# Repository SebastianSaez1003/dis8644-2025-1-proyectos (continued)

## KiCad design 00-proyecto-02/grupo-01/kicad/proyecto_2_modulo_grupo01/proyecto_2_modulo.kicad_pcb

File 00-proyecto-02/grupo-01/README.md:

# proyecto-02

## Acerca del proyecto

- Grupo: 01
- Integrantes:
  - Emilia Contreras / [hazzaily](https://github.com/hazzaily)
  - Katalina Riquelme / [katalinariquelme](https://github.com/katalinariquelme)
  - Thyare Santander / [thyare08](https://github.com/thyare08)
- Chips usados:
  - Chip 555
  - Chip 4017
  - Chip LM324

## Presentación textual

Luz de noche en secuencia gradual con forma de nube.

El proyecto consiste en un detector de sombra invertido que enciende una lámpara que posee una secuencia gradual.

## Dibujos de diagramas del circuito (1 punto)

Este es el diagrama a mano.

En este  dibujo mostramos en orden cómo se efectúa la secuencia de luces o no, según sea que esté en una habitación con luz u oscuridad.

## Prototipado de circuitos en protoboard (1 punto)

A continuación se presentan imágenes de las protoboards usadas.

En la protoboard larga está configurado el detector de sombras, en el cual se utiliza un LDR para encender si está oscuro y apagarse si hay luz. Luego viene el chip 555 con un potenciómetro que regula la intesidad de la luz, continuando con un LM324 que crea la secuencia de las luces. Finalizamos el circuito de salida usando transistores que hicieron que al encender y apagarlos LED se prendieran y apagaran de manera gradual.

## Bill of Materials (1 punto)

| Reference                                       | Value   | Qty |
|-------------------------------------------------|---------|-----|
| C1,C3,C4                                        | 10uF    | 3   |
| C2                                              | 103n    | 1   |
| C7,C8,C9,C10,C11,C12                            | 220uF   | 6   |
| D5,D6,D7,D8,D9,D10,D11,D12,D13,D14,D15,D16      | LED 5mm | 12  |
| J1                                              | ph-2    | 1   |
| J5,J6,J7                                        | ph-3    | 2   |
| J21,J23                                         | mod1    | 2   |
| J22,J24                                         | mod2    | 2   |
| J25,J26                                         | mod3    | 2   |
| Q2,Q3,Q4                                        | 2n2222  | 3   |
| R1,R3,R4,R7,R8                                  | 10k     | 5   |
| R2                                              | LDR     | 1   |
| R5                                              | 100K    | 1   |
| R15,R17,R22,R25,R27,R31                         | 47K     | 6   |
| R16,R18,R19,R20,R21,R23,R24,R26,R28,R29,R30,R32 | 1K      | 12  |
| RV1,RV2                                         | 500K    | 2   |
| U1                                              | LM324   | 1   |
| U2                                              | 555     | 1   |
| U3                                              | 4017    | 1   |

## Ayudas y comunicación con colegas (1 punto)

[FranUDP](https://github.com/FranUDP) nos ayudó a revisar nuestro esquemático, a buscar y asignar huellas, y además de ayudarnos a resolver dudas sobre la PCB.

[Bernardita-lobo](https://github.com/Bernardita-lobo) y [jotamorales-romulus](https://github.com/jotamorales-romulus) nos ayudaron con el registro fotográfico de nuestra protoboard.

[duckusu](https://github.com/duckusu) nos ayudó a busacr lugares en donde podríamos comprar materiales faltantes, y por mayor.

Ayudamos a [antocristi](https://github.com/antocristi) y a [paulinavargasf](https://github.com/paulinavargasf) del grupo 05 a saber cómo subir fotos a los archivos de github.

## Esquematico en Kicad (1 punto)

El esquemático comienza con un chip LM324, el cual funciona como detector de luz, esto porque es la configuración inicial de un detector de sombra, pero con R1 y R2 intercambiados, logrando así que el circuito se encienda cuando no haya luz estimulando el LDR. El chip siguiente es un 555 configurado en modo astable, lo que nos permite controlar la velocidad con la que cambia la "tira de LED" a la siguiente. Seguido de esto tenemos un chip 4017 que funciona como secuenciador, siendo esta secuencia de "tiras de LED" la que controla el chip anterior. Por último, gracias al uso de transistores es que logramos una iluminación que va de menor a mayor, y cuando se apaga de mayor a menor, generando una onda que cambia suavemente y no de manera abrupta.

## PCB en Kicad (1 punto)

## Recursos adicionales

## Bibliografía

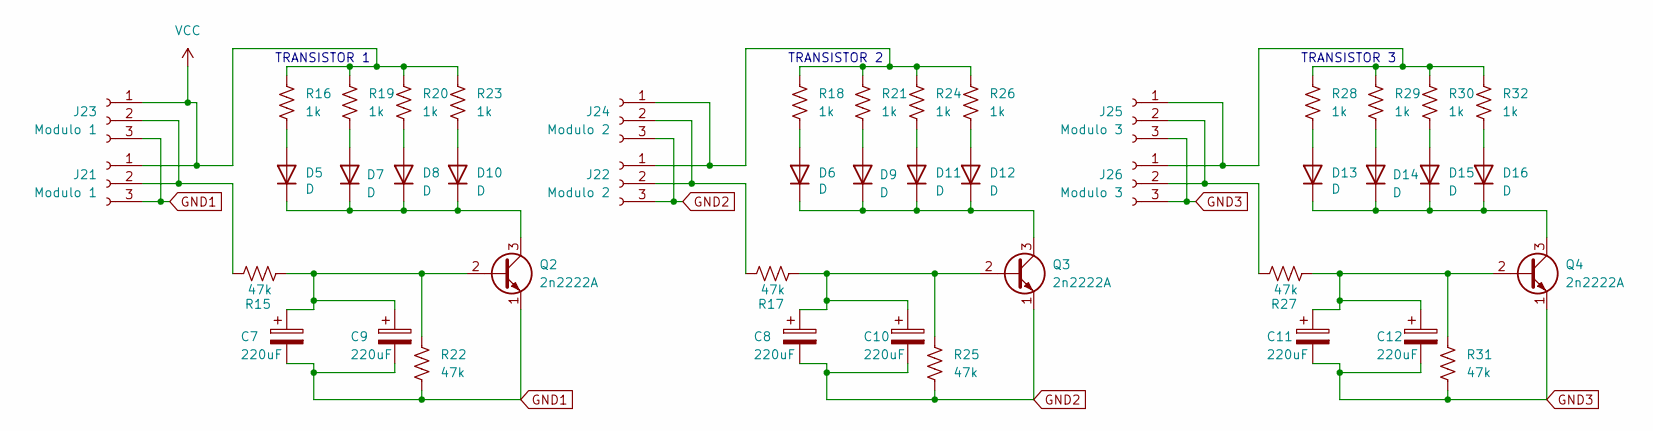
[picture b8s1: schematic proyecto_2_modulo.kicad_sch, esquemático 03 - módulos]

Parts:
C7, C8, C9, C10, C11, C12: 220uF; CP_Radial_D6.3mm_P2.50mm
D5, D6, D7, D8, D9, D10, D11, D12, D13, D14, D15, D16: D; LED_D5.0mm
J21, J23: Modulo 1; PinHeader_1x03_P2.54mm_Vertical
J22, J24: Modulo 2; PinHeader_1x03_P2.54mm_Vertical
J25, J26: Modulo 3; PinHeader_1x03_P2.54mm_Vertical
Q2, Q3, Q4: 2n2222A; TO-92
R15, R17, R22, R25, R27, R31: 47k; R_Axial_DIN0207_L6.3mm_D2.5mm_P10.16mm_Horizontal
R16, R18, R19, R20, R21, R23, R24, R26, R28, R29, R30, R32: 1k; R_Axial_DIN0207_L6.3mm_D2.5mm_P10.16mm_Horizontal

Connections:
GND1: C7.2, C9.2, J21.3, J23.3, Q2.1 (E), R22.2
GND2: C8.2, C10.2, J22.3, J24.3, Q3.1 (E), R25.2
GND3: C11.2, C12.2, J25.3, J26.3, Q4.1 (E), R31.2
unnamed: D5.2 (A), R16.2
unnamed: D6.2 (A), R18.2
unnamed: D7.2 (A), R19.2
unnamed: D8.2 (A), R20.2
unnamed: D9.2 (A), R21.2
unnamed: D10.2 (A), R23.2
unnamed: D5.1 (K), D7.1 (K), D8.1 (K), D10.1 (K), Q2.3 (C)
unnamed: D11.2 (A), R24.2
unnamed: D6.1 (K), D9.1 (K), D11.1 (K), D12.1 (K), Q3.3 (C)
unnamed: D12.2 (A), R26.2
unnamed: D13.2 (A), R28.2
unnamed: D13.1 (K), D14.1 (K), D15.1 (K), D16.1 (K), Q4.3 (C)
unnamed: D14.2 (A), R29.2
unnamed: D15.2 (A), R30.2
unnamed: D16.2 (A), R32.2
unnamed: J21.2, J23.2, R15.1
unnamed: J22.1, J24.1, R18.1, R21.1, R24.1, R26.1
unnamed: J22.2, J24.2, R17.1
unnamed: J25.1, J26.1, R28.1, R29.1, R30.1, R32.1
unnamed: J25.2, J26.2, R27.1
unnamed: C7.1, C9.1, Q2.2 (B), R15.2, R22.1
unnamed: C8.1, C10.1, Q3.2 (B), R17.2, R25.1
unnamed: C11.1, C12.1, Q4.2 (B), R27.2, R31.1
VCC: J21.1, J23.1, R16.1, R19.1, R20.1, R23.1

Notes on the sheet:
TRANSISTOR 3
TRANSISTOR 2
TRANSISTOR 1

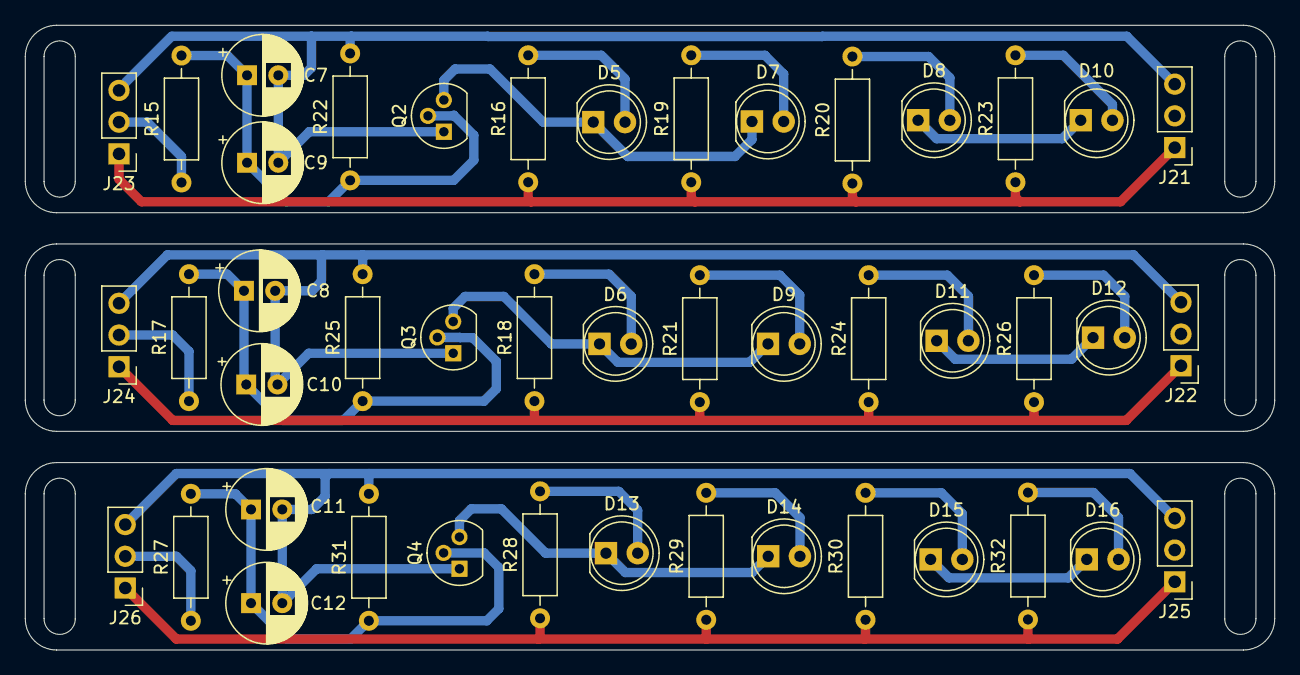
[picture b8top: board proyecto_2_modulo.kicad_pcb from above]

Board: 2 copper layers, 100.0 x 50.0 mm, 45 parts (0 on the bottom side), 27 nets.

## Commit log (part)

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2025-07-08 Create a
2025-07-08 Update README.md
    Ajuste bibliografía
2025-07-08 Update README.md
    Ajuste de bibliografía
2025-07-09 corregir MD056
2025-07-09 Create pcb
2025-07-09 agregar alt-text
2025-07-09 examen
2025-07-10 agregar links examen y borrar proyecto-01
2025-07-10 agregar mas enlaces
2025-07-10 Ajuste markdown
2025-07-10 Ajustes de markdown / correción de espaciado
2025-07-10 Ajustes ortografía
2025-07-10 Ajuste ortografía
2025-07-10 Create kicad
2025-07-10 examen grupo-00a PARTE-01
2025-07-10 ArregloMarkdown
2025-07-10 Añadido esqueleto por rellenar
2025-07-10 corregir MD036
2025-07-10 corregir errores MD036
2025-07-10 Ajuste nombres
2025-07-10 agregar retroalim Camila-Parada
2025-07-10 Ajustes ortografía y markdown
2025-07-10 Ajustes redacción
2025-07-10 Título
2025-07-10 Añadido texto descripción curso
2025-07-10 Ajuste lint
2025-07-10 Eliminar imagenes repetidas
2025-07-10 archivo nombre cambiado
2025-07-10 Add files
2025-07-10 Ajuste redacción
2025-07-10 Subir archivos documentación
2025-07-10 agregar cambios duckusu
2025-07-10 corregir filenames duckusu
2025-07-10 corregir nombres de archivos duckusu
2025-07-10 agregar retroalim
2025-07-10 Detalles imágenes
2025-07-10 Añadir imágenes
2025-07-10 Añadir referencias
2025-07-10 Rename 00-examen/grupo-03/imagenes/grupo03-esquematico-chip4017.png to 00-examen/grupo-03/imagenes/kicad/grupo03-esquematico-chip4017.png
2025-07-10 Rename 00-examen/grupo-03/imagenes/grupo03-esquematico-chipLM324.png to 00-examen/grupo-03/imagenes/kicad/grupo03-esquematico-chipLM324.png
2025-07-10 Rename 00-examen/grupo-03/imagenes/grupo03-esquematico-kicad01.pdf to 00-examen/grupo-03/imagenes/kicad/grupo03-esquematico-kicad01.pdf
2025-07-10 Rename 00-examen/grupo-03/imagenes/grupo03-pcb-kicad02.jpg to 00-examen/grupo-03/imagenes/kicad/grupo03-pcb-kicad02.jpg
2025-07-10 Rename 00-examen/grupo-03/imagenes/grupo03-pcb-kicad03.jpg to 00-examen/grupo-03/imagenes/kicad/grupo03-pcb-kicad03.jpg
2025-07-10 Rename 00-examen/grupo-03/imagenes/grupo03-pcb-kicad04.jpg to 00-examen/grupo-03/imagenes/kicad/grupo03-pcb-kicad04.jpg
2025-07-10 Rename 00-examen/grupo-03/imagenes/grupo03-pcb-kicad05.pdf to 00-examen/grupo-03/imagenes/kicad/grupo03-pcb-kicad05.pdf
2025-07-11 Correción markdown lint
2025-07-11 Exame grupo-00a-Parte02
2025-07-11 cambios en examen-grupo-00a
2025-07-11 Create montaje
2025-07-11 corregir MD001
2025-07-11 Create carpeta
2025-07-11 cambios
2025-07-11 corregir errores md grupo 04
2025-07-11 Rename 00-examen/grupo-03/imagenes/grupo03-carcasa01.jpg to 00-examen/grupo-03/imagenes/carcasa/grupo03-carcasa01.jpg
2025-07-11 Rename 00-examen/grupo-03/imagenes/grupo03-carcasa02.jpg to 00-examen/grupo-03/imagenes/carcasa/grupo03-carcasa02.jpg
2025-07-11 Rename 00-examen/grupo-03/imagenes/grupo03-montaje01.jpg to 00-examen/grupo-03/imagenes/montaje/grupo03-montaje01.jpg
2025-07-11 Rename 00-examen/grupo-03/imagenes/grupo03-montaje02.jpg to 00-examen/grupo-03/imagenes/montaje/grupo03-montaje02.jpg
2025-07-11 Rename 00-examen/grupo-03/imagenes/grupo03-protoboardjpg.jpg to 00-examen/grupo-03/imagenes/protoboard/grupo03-protoboardjpg.jpg
2025-07-11 Rename 00-examen/grupo-03/imagenes/grupo03-proceso.jpg to 00-examen/grupo-03/imagenes/proceso/grupo03-proceso.jpg
2025-07-11 reitengrar apuntes carlo
2025-07-11 Create borrar
2025-07-11 Create modelo3d
2025-07-11 imagenes de procesos
    imagenes de nuestro proceso del proyecto 2
2025-07-11 Agregas descripciones de grupo-03
2025-07-11 modelos 3d
    fotos de los modelos 3d
2025-07-11 mas fotos
2025-07-11 casco en cabeza imagen
2025-07-11 0c - FranUDP
2025-07-11 fotos matril carcasas tpu
2025-07-14 borrar HTML para img
